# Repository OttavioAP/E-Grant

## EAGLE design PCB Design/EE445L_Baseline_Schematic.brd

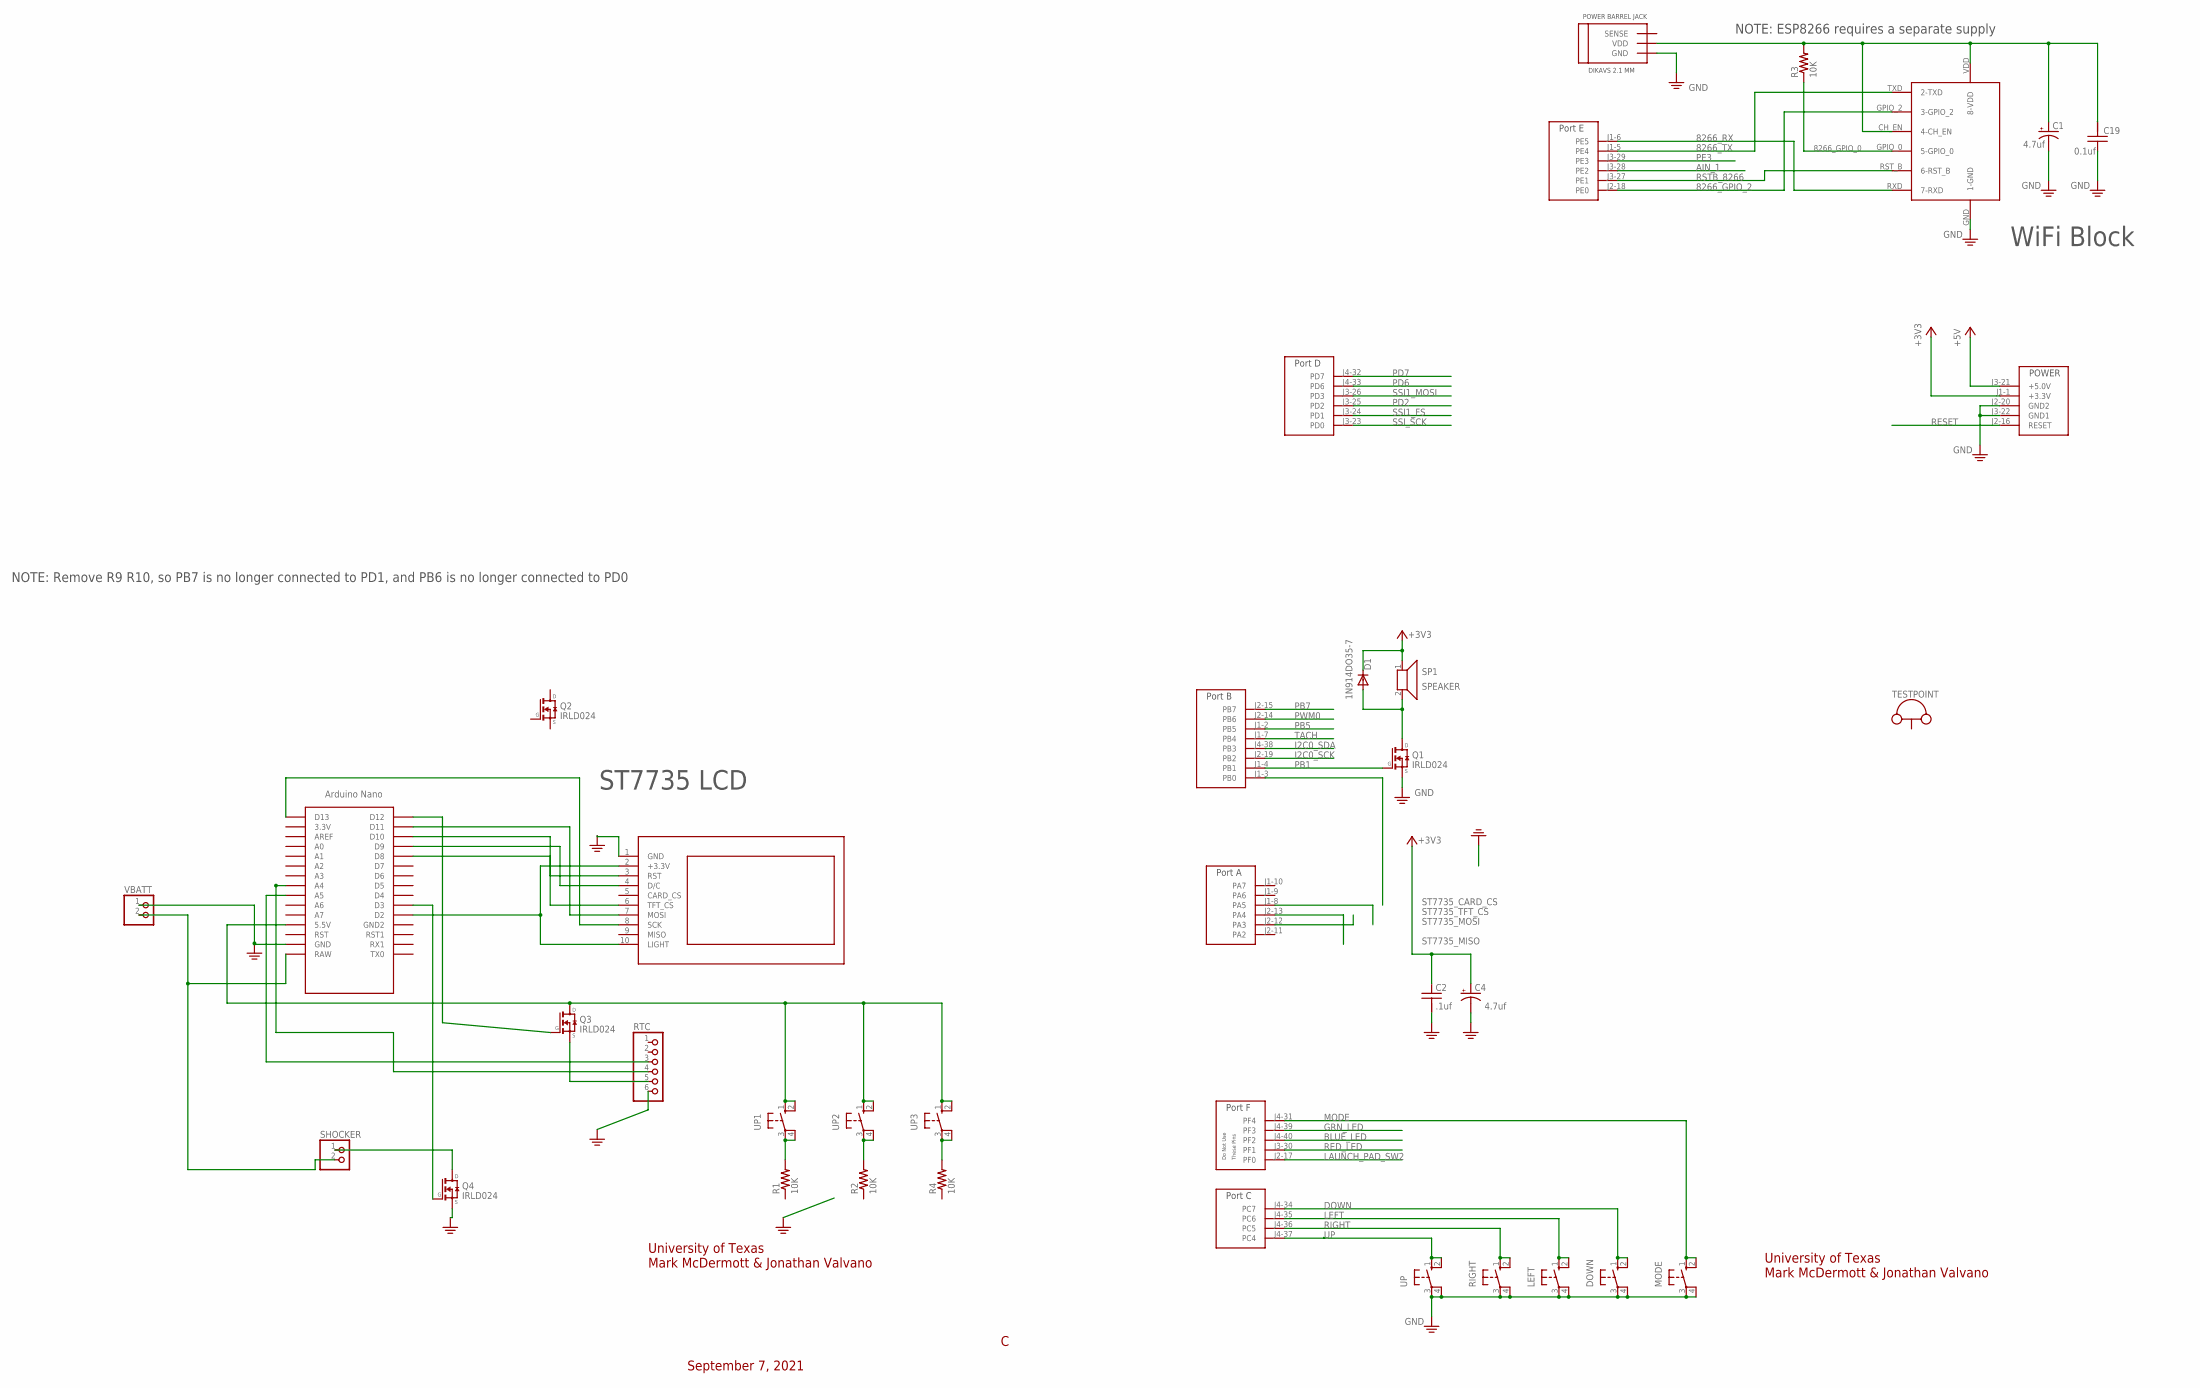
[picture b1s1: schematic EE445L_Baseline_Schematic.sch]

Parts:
C1, C4: 4.7uf; CAP200MILPOLARIZED
C2: .1uf; CAP200MIL
C19: 0.1uf; CAP200MIL
D1: 1N914DO35-7; DO35-7
DOWN: B3F-1052; B3F-10XX
LEFT: B3F-1052; B3F-10XX
MODE: B3F-1052; B3F-10XX
Q1, Q2, Q3, Q4: IRLD024
R1, R2, R3, R4: 10K; RES300MIL
RIGHT: B3F-1052; B3F-10XX
RTC: PINHD-1X6; 1X06
SHOCKER: PINHD-1X2; 1X02
SP1: SPEAKER; 1X02
TESTPOINT: TP_LOOP
U$1: ESP_8266; ESP8266
U$2: TM4C_BP; TM4C_BOOSTER_PACK
U$3: ST7735
U$4: 2.1MM_BARREL_JACK; 2.1M_BARREL_JACK
U$5: NANO
UP, UP1, UP2, UP3: B3F-1052; B3F-10XX
VBATT: PINHD-1X2; 1X02

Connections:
8266_GPIO_0: R3.1, U$1.GPIO_0 (5-GPIO_0)
8266_GPIO_2: U$1.GPIO_2 (3-GPIO_2), U$2.J2-18 (PE0)
8266_RX: U$1.RXD (7-RXD), U$2.J1-6 (PE5)
8266_TX: U$1.TXD (2-TXD), U$2.J1-5 (PE4)
+3V3: C2.1, C4.+, D1.C, SP1.1, U$2.J1-1 (+3.3V)
+5V: U$2.J3-21 (+5.0V)
AIN_1: U$2.J3-28 (PE2)
BLUE_LED: U$2.J4-40 (PF2)
DOWN: DOWN.1 (S), DOWN.2 (S1), U$2.J4-34 (PC7)
GND: C1.-, C2.2, C4.-, C19.1, DOWN.3, DOWN.4 (P1), LEFT.3, LEFT.4 (P1), MODE.3, MODE.4 (P1), Q1.P$4 (S), Q4.P$4 (S), RIGHT.3, RIGHT.4 (P1), RTC.6, U$1.GND (1-GND), U$2.J2-20 (GND2), U$2.J3-22 (GND1), U$3.1 (GND), U$4.GND, U$5.GND, UP.3, UP.4 (P1), VBATT.1
GND1: R1.2, UP1.3, UP1.4 (P1)
GND2: R2.2, UP2.3, UP2.4 (P1)
GND3: R4.2, UP3.3, UP3.4 (P1)
GRN_LED: U$2.J4-39 (PF3)
I2C0_SCK: U$2.J2-19 (PB2)
I2C0_SDA: U$2.J4-38 (PB3)
LAUNCH_PAD_SW2: U$2.J2-17 (PF0)
LEFT: LEFT.1 (S), LEFT.2 (S1), U$2.J4-35 (PC6)
MODE: MODE.1 (S), MODE.2 (S1), U$2.J4-31 (PF4)
unnamed: D1.A, Q1.P$1 (D), SP1.2
unnamed: C1.+, C19.2, R3.2, U$1.CH_EN (4-CH_EN), U$1.VDD (8-VDD), U$4.VDD
unnamed: SHOCKER.2, U$5.RAW, VBATT.2
unnamed: U$3.8 (SCK), U$5.D13
unnamed: U$3.7 (MOSI), U$5.D11
unnamed: U$3.4 (D/C), U$5.D9
unnamed: U$3.3 (RST), U$5.D8
unnamed: U$3.6 (TFT_CS), U$5.D10
unnamed: U$3.2 (+3.3V), U$3.10 (LIGHT), U$5.D2
unnamed: RTC.4, U$5.A4
unnamed: RTC.3, U$5.A5
unnamed: Q3.P$3 (G), U$5.D12
unnamed: Q3.P$4 (S), RTC.5
unnamed: Q4.P$3 (G), U$5.D3
unnamed: Q4.P$1 (D), SHOCKER.1
PB1: Q1.P$3 (G), U$2.J1-4 (PB1)
PB5: U$2.J1-2 (PB5)
PB7: U$2.J2-15 (PB7)
PD2: U$2.J3-25 (PD2)
PD6: U$2.J4-33 (PD6)
PD7: U$2.J4-32 (PD7)
PE3: U$2.J3-29 (PE3)
PWM0: U$2.J2-14 (PB6)
RED_LED: U$2.J3-30 (PF1)
RESET: U$2.J2-16 (RESET)
RIGHT: RIGHT.1 (S), RIGHT.2 (S1), U$2.J4-36 (PC5)
RSTB_8266: U$1.RST_B (6-RST_B), U$2.J3-27 (PE1)
SSI1_FS: U$2.J3-24 (PD1)
SSI1_MOSI: U$2.J3-26 (PD3)
SSI_SCK: U$2.J3-23 (PD0)
ST7735_CARD_CS: U$2.J1-3 (PB0)
ST7735_MISO: U$2.J2-13 (PA4)
ST7735_MOSI: U$2.J1-8 (PA5)
ST7735_TFT_CS: U$2.J2-12 (PA3)
TACH: U$2.J1-7 (PB4)
UP: U$2.J4-37 (PC4), UP.1 (S), UP.2 (S1)
UP1: Q3.P$1 (D), U$5.5V (5.5V), UP1.1 (S), UP1.2 (S1), UP2.1 (S), UP2.2 (S1), UP3.1 (S), UP3.2 (S1)

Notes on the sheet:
WiFi Block
University of Texas Mark McDermott & Jonathan Valvano
September 7, 2021
NOTE: ESP8266 requires a separate supply
NOTE: Remove R9 R10, so PB7 is no longer connected to PD1, and PB6 is no longer connected to PD0
ST7735 LCD

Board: 2 copper layers, 31 parts (0 on the bottom side), 32 nets, no tracks yet.

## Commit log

2023-02-28 starting new version
2023-02-28 made progress
2023-02-28 basically works
2023-02-28 works but sucks
